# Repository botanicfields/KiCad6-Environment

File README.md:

# KiCad6-Environment
My symbols, my footprints, my templates, etc. of KiCad6  
KiCad6 による基板の設計時に作成したライブラリやテンプレートを置いています。
## 1．symbols
「シンボルエディター」で作成したシンボルのライブラリです。
### (1) @bf.kicad_sym
使用しているシンボルのうち、独自に作成したシンボルの全てを含みます。
## 2．footprints
「フットプリントエディター」で作成したフットプリントのライブラリです。
### (1) @bf.pretty
使用しているフットプリントのうち、独自に作成したフットプリントの全てを含みます。
## 3．template
「KiCadマネージャー」において「テンプレートから新規プロジェクトを作成..」で選択可能となる「ユーザーテンプレート」のデータです。
### (1) M5Stack_module
M5Stack用のモジュール基板のテンプレートです。M-BUSのピンヘッダーとピンソケットの両方を備え、モジュールの積み重ねに対応します。フレームにはM5Stack社のPROTOモジュールのモールドを流用することを想定しています。
- 基板の厚さは1mmです

### (2) M5Stack_module_fdm
M5Stack用のモジュール基板のテンプレートです。M-BUSのピンヘッダーとピンソケットの両方を備え、モジュールの積み重ねに対応します。フレームにはFDMによるモールドを使用することを想定し、四隅に逃げがあります。
- 基板の厚さは1mmです
- FDM: Fused Deposition Modeling

### (3) M5Stack_bottom_fdm
M5Stack用のボトム基板のテンプレートです。M-BUSのピンヘッダーがありますがピンソケットはありません。フレームにはFDMによるモールドを使用することを想定し、四隅に逃げがあります。
- FDM: Fused Deposition Modeling

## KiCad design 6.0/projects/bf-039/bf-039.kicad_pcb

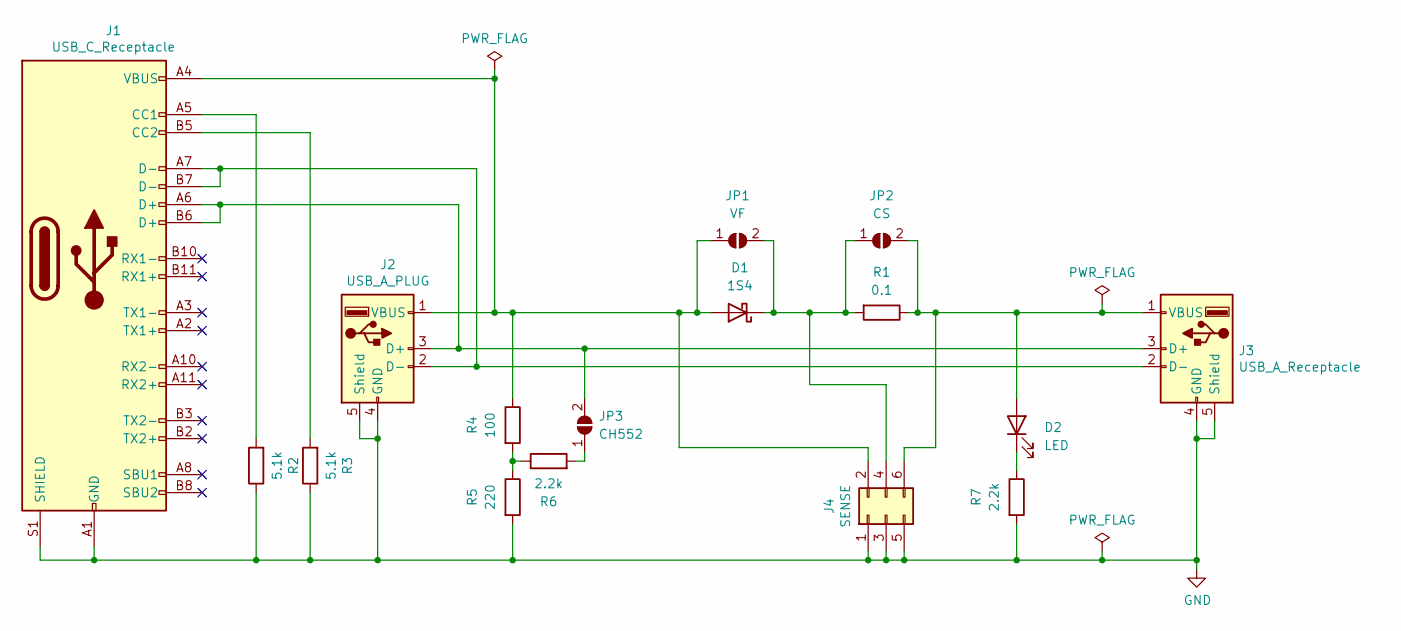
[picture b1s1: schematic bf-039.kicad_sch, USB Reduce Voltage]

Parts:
D1: 1S4; D_DO-41_SOD81_P10.16mm_Horizontal
D2: LED; LED_0603_1608Metric
J1: USB_C_Receptacle; BF@USB-C-5077CR-16-SMC2-BK-TR
J2: USB_A_PLUG; BF@USB-4AM103
J3: USB_A_Receptacle; BF@USB-4AF103BS
J4: SENSE; PinSocket_2x03_P2.54mm_Vertical
JP1: VF; SolderJumper-2_P1.3mm_Open_RoundedPad1.0x1.5mm
JP2: CS; SolderJumper-2_P1.3mm_Open_RoundedPad1.0x1.5mm
JP3: CH552; SolderJumper-2_P1.3mm_Open_RoundedPad1.0x1.5mm
R1: 0.1; R_Axial_DIN0207_L6.3mm_D2.5mm_P10.16mm_Horizontal
R2, R3: 5.1k; R_0603_1608Metric
R4: 100; R_0603_1608Metric
R5: 220; R_0603_1608Metric
R6, R7: 2.2k; R_0603_1608Metric

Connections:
GND: J1.A1 (GND), J1.A12 (GND), J1.B1 (GND), J1.B12 (GND), J1.S1 (SHIELD), J2.4 (GND), J2.5 (Shield), J3.4 (GND), J3.5 (Shield), J4.1, J4.3, J4.5, R2.1, R3.1, R5.2, R7.2
unnamed: D1.1 (K), J4.4, JP1.2 (B), JP2.1 (A), R1.2
unnamed: D1.2 (A), J1.A4 (VBUS), J1.A9 (VBUS), J1.B4 (VBUS), J1.B9 (VBUS), J2.1 (VBUS), J4.2, JP1.1 (A), R4.1
unnamed: D2.1 (K), R7.1
unnamed: D2.2 (A), J3.1 (VBUS), J4.6, JP2.2 (B), R1.1
unnamed: J1.A5 (CC1), R2.2
unnamed: J1.A6 (D+), J1.B6 (D+), J2.3 (D+), J3.3 (D+), JP3.2 (B)
unnamed: J1.A7 (D-), J1.B7 (D-), J2.2 (D-), J3.2 (D-)
unnamed: J1.B5 (CC2), R3.2
unnamed: JP3.1 (A), R6.2
unnamed: R4.2, R5.1, R6.1

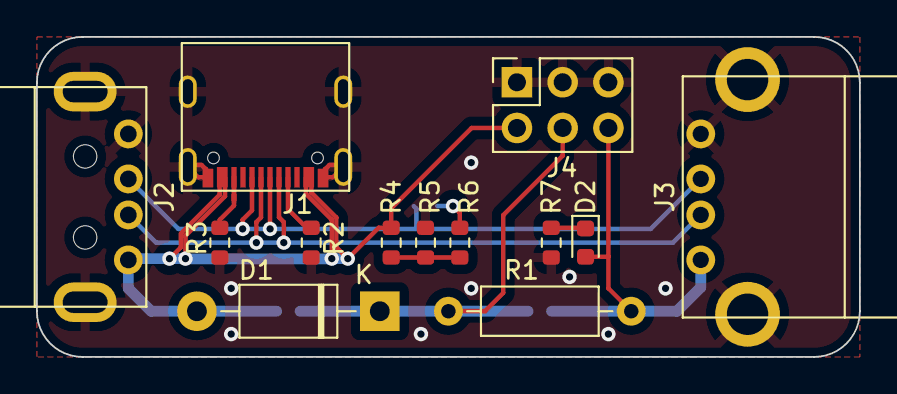
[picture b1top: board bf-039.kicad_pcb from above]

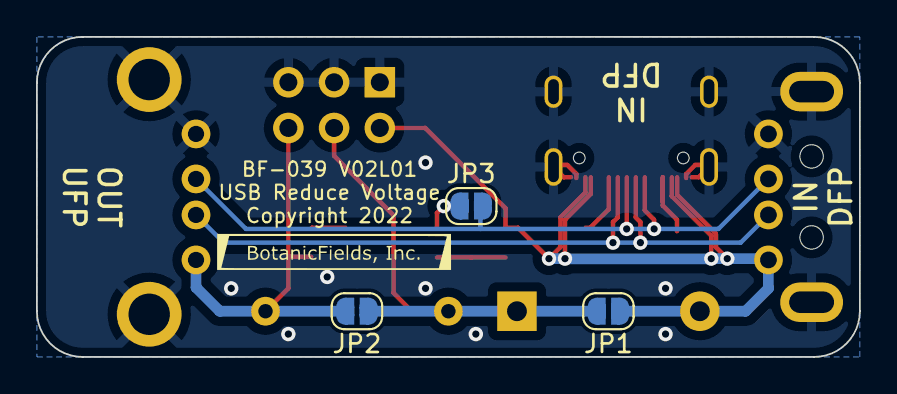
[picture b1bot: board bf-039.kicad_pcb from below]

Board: 2 copper layers, 45.7 x 17.8 mm, 16 parts (3 on the bottom side), 11 nets.

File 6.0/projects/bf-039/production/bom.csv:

Designator,Footprint,Quantity,Value,LCSC Part #
D1,D_DO-41_SOD81_P10.16mm_Horizontal,1,1S4,
D2,LED_0603_1608Metric,1,LED,C72041
J1,BF@USB-C-5077CR-16-SMC2-BK-TR,1,USB_C_Receptacle,
J2,BF@USB-4AM103,1,USB_A_PLUG,
J3,BF@USB-4AF103BS,1,USB_A_Receptacle,
J4,PinSocket_2x03_P2.54mm_Vertical,1,SENSE,
JP1,SolderJumper-2_P1.3mm_Open_RoundedPad1.0x1.5mm,1,VF,
JP2,SolderJumper-2_P1.3mm_Open_RoundedPad1.0x1.5mm,1,CS,
JP3,SolderJumper-2_P1.3mm_Open_RoundedPad1.0x1.5mm,1,CH552,
R1,R_Axial_DIN0207_L6.3mm_D2.5mm_P10.16mm_Horizontal,1,0.1,
"R2, R3",R_0603_1608Metric,2,5.1k,C23186
R4,R_0603_1608Metric,1,100,C21190
R5,R_0603_1608Metric,1,220,C22962
"R6, R7",R_0603_1608Metric,2,2.2k,C4190

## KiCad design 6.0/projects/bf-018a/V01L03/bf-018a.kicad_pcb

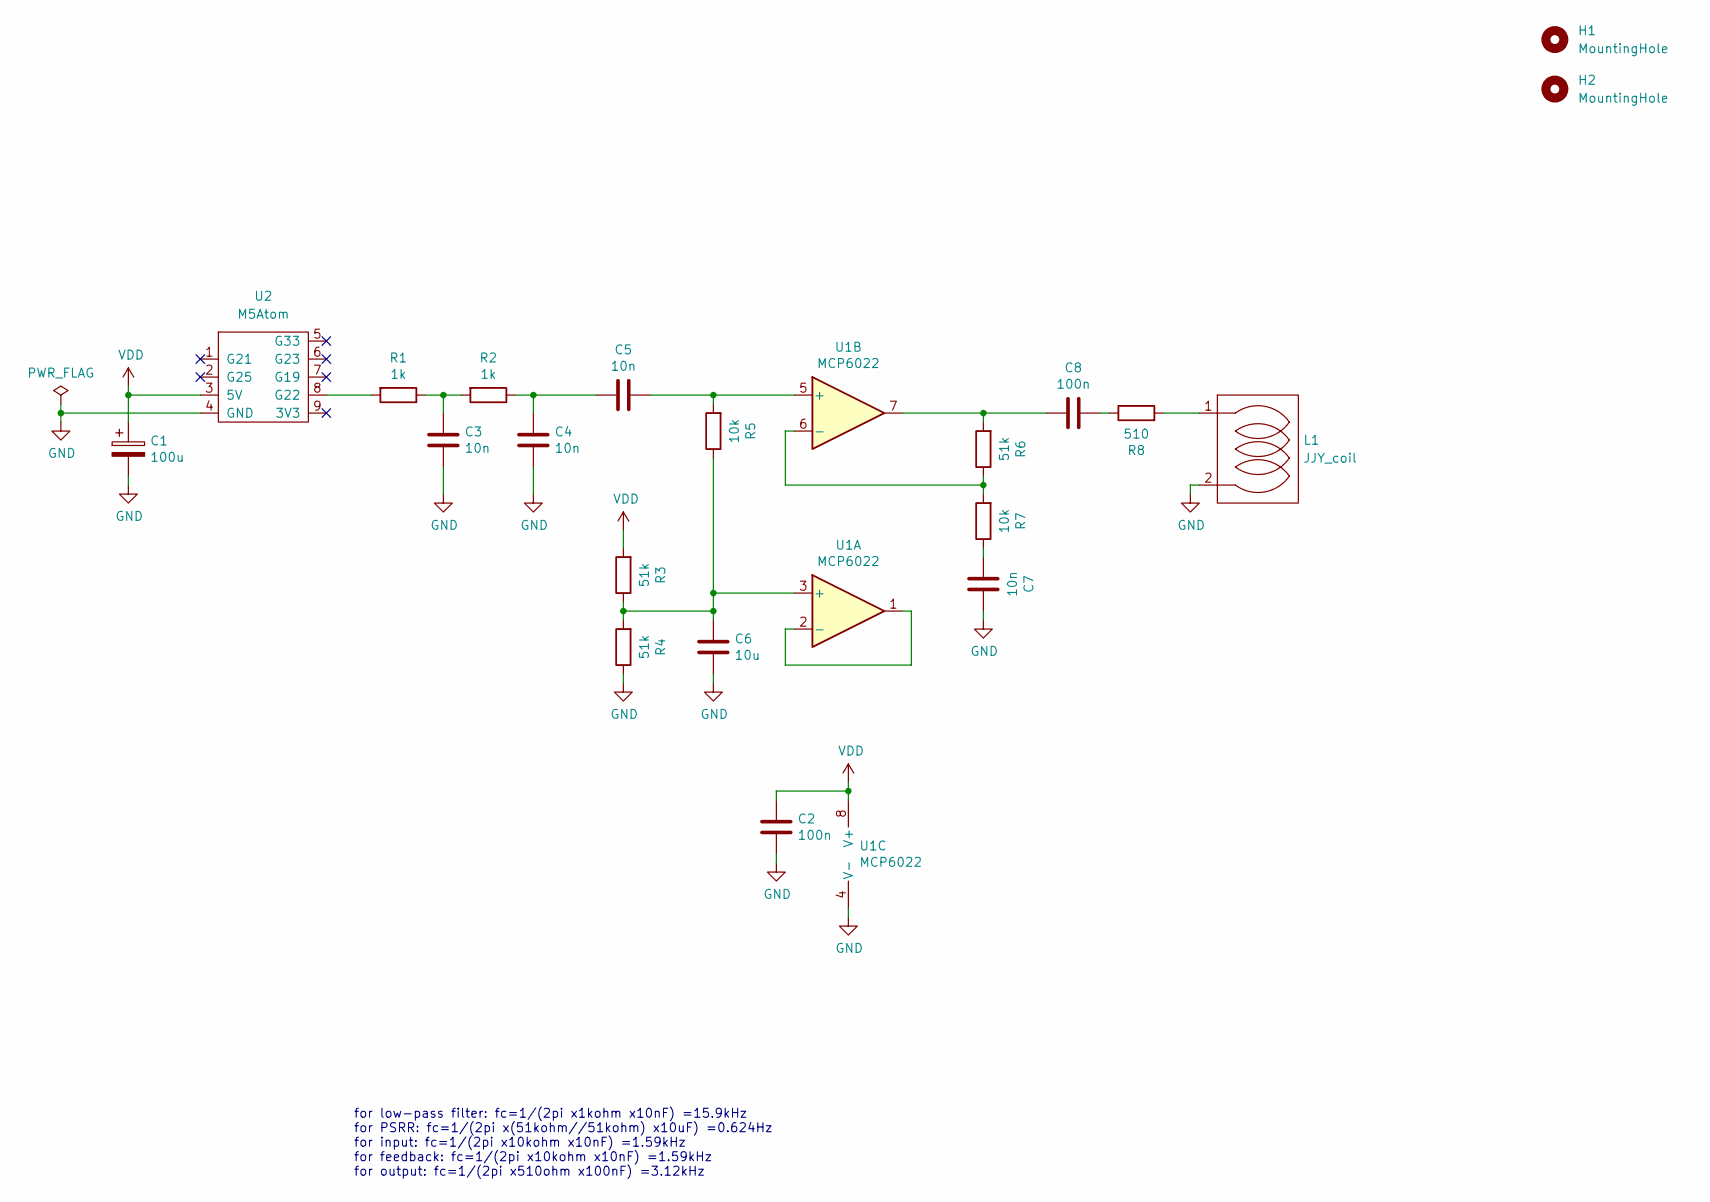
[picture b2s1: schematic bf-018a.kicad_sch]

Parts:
C1: 100u; CP_Elec_6.3x7.7
C2, C8: 100n; C_0603_1608Metric
C3, C4, C5, C7: 10n; C_0603_1608Metric
C6: 10u; C_0603_1608Metric
H1, H2: MountingHole; MountingHole_2.5mm
L1: JJY_coil; BF@JJY_Coil
R1, R2: 1k; R_0603_1608Metric
R3, R4, R6: 51k; R_0603_1608Metric
R5, R7: 10k; R_0603_1608Metric
R8: 510; R_1206_3216Metric
U1: MCP6022; SOIC-8_3.9x4.9mm_P1.27mm
U2: M5Atom; BF@M5Atom

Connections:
GND: C1.2, C2.1, C3.1, C4.1, C6.1, C7.1, L1.2, R4.1, U1.4 (V-), U2.4 (GND)
unnamed: C3.2, R1.1, R2.2
unnamed: C4.2, C5.2, R2.1
unnamed: C5.1, R5.2, U1.5 (+)
unnamed: C6.2, R3.1, R4.2, R5.1, U1.3 (+)
unnamed: C7.2, R7.1
unnamed: C8.1, R8.1
unnamed: C8.2, R6.2, U1.7
unnamed: L1.1, R8.2
unnamed: R1.2, U2.8 (G22)
unnamed: R6.1, R7.2, U1.6 (-)
unnamed: U1.1, U1.2 (-)
VDD: C1.1, C2.2, R3.2, U1.8 (V+), U2.3 (5V)

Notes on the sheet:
for low-pass filter: fc=1/(2pi x1kohm x10nF) =15.9kHz for PSRR: fc=1/(2pi x(51kohm//51kohm) x10uF) =0.624Hz for input: fc=1/(2pi x10kohm x10nF) =1.59kHz for feedback: fc=1/(2pi x10kohm x10nF) =1.59kHz for output: fc=1/(2pi x510ohm x100nF) =3.12kHz

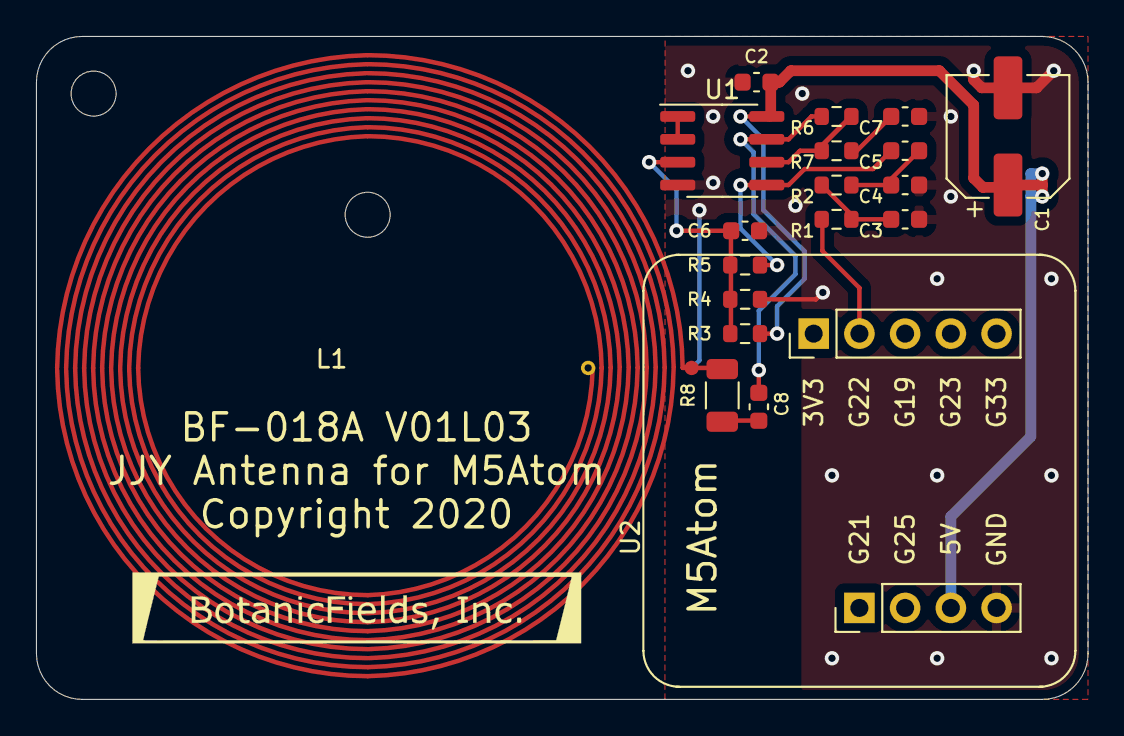
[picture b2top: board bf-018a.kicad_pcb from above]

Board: 2 copper layers, 58.4 x 36.8 mm, 21 parts (0 on the bottom side), 13 nets.

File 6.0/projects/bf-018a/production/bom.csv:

Designator,Footprint,Quantity,Value,LCSC Part #
"C1_12, C1_11, C1_10, C1_9, C1_8, C1_7, C1_6, C1_5, C1_4, C1_3, C1_2, C1",CP_Elec_6.3x7.7,12,100u,C176674
"C2_12, C2_11, C2_10, C2_9, C2_8, C2_7, C2_6, C2_5, C2_4, C2_3, C2_2, C2, C8_12, C8_11, C8_10, C8_9, C8_8, C8_7, C8_6, C8_5, C8_4, C8_3, C8_2, C8",C_0603_1608Metric,24,100n,C14663
"C3_12, C3_11, C3_10, C3_9, C3_8, C3_7, C3_6, C3_5, C3_4, C3_3, C3_2, C3, C4_12, C4_11, C4_10, C4_9, C4_8, C4_7, C4_6, C4_5, C4_4, C4_3, C4_2, C4, C5_12, C5_11, C5_10, C5_9, C5_8, C5_7, C5_6, C5_5, C5_4, C5_3, C5_2, C5, C7_12, C7_11, C7_10, C7_9, C7_8, C7_7, C7_6, C7_5, C7_4, C7_3, C7_2, C7",C_0603_1608Metric,48,10n,C57112
"C6_12, C6_11, C6_10, C6_9, C6_8, C6_7, C6_6, C6_5, C6_4, C6_3, C6_2, C6",C_0603_1608Metric,12,10u,C19702
"H1_12, H1_11, H1_10, H1_9, H1_8, H1_7, H1_6, H1_5, H1_4, H1_3, H1_2, H1, H2_12, H2_11, H2_10, H2_9, H2_8, H2_7, H2_6, H2_5, H2_4, H2_3, H2_2, H2",MountingHole_2.5mm,24,MountingHole,
"L1_12, L1_11, L1_10, L1_9, L1_8, L1_7, L1_6, L1_5, L1_4, L1_3, L1_2, L1",BF@JJY_Coil,12,JJY_coil,
"R1_12, R1_11, R1_10, R1_9, R1_8, R1_7, R1_6, R1_5, R1_4, R1_3, R1_2, R1, R2_12, R2_11, R2_10, R2_9, R2_8, R2_7, R2_6, R2_5, R2_4, R2_3, R2_2, R2",R_0603_1608Metric,24,1k,C21190
"R3_12, R3_11, R3_10, R3_9, R3_8, R3_7, R3_6, R3_5, R3_4, R3_3, R3_2, R3, R4_12, R4_11, R4_10, R4_9, R4_8, R4_7, R4_6, R4_5, R4_4, R4_3, R4_2, R4, R6_12, R6_11, R6_10, R6_9, R6_8, R6_7, R6_6, R6_5, R6_4, R6_3, R6_2, R6",R_0603_1608Metric,36,51k,C23196
"R5_12, R5_11, R5_10, R5_9, R5_8, R5_7, R5_6, R5_5, R5_4, R5_3, R5_2, R5, R7_12, R7_11, R7_10, R7_9, R7_8, R7_7, R7_6, R7_5, R7_4, R7_3, R7_2, R7",R_0603_1608Metric,24,10k,C25804
"R8_12, R8_11, R8_10, R8_9, R8_8, R8_7, R8_6, R8_5, R8_4, R8_3, R8_2, R8",R_1206_3216Metric,12,510,C17991
"U1_12, U1_11, U1_10, U1_9, U1_8, U1_7, U1_6, U1_5, U1_4, U1_3, U1_2, U1",SOIC-8_3.9x4.9mm_P1.27mm,12,MCP6022,C57639
"U2_12, U2_11, U2_10, U2_9, U2_8, U2_7, U2_6, U2_5, U2_4, U2_3, U2_2, U2",BF@M5Atom,12,M5Atom,

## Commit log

2022-10-22 templetes of M5stack
    The first upload
2022-10-22 Update README.md
    minimum description
2022-10-22 template M5Stack
    add images
2022-10-23 template M5Stack
    M-BUS connector U1 to J1
2022-11-09 bf-039
    example USB-C
2022-11-09 .gitignore
    comment out .csv
2022-12-05 BF-018A
    add BF-018A
2022-12-17 BF@SW_Slide_1P2T_CK_OS102011MA1Q.kicad_mod
    F.SilkS updated

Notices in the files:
6.0/projects/bf-018a/V01L03/bf-018a.kicad_pcb:
Copyright 2020 BotanicFields, Inc.
6.0/projects/bf-039/bf-039.kicad_pcb:
Copyright 2022 BotanicFields, Inc.
